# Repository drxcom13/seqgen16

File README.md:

# SeqGen16 – 16-kanałowy cyfrowy generator sekwencji (MAX 10 10M08 Eval Kit)

## Założenia projektu

1. **16 niezależnych kanałów** wyjściowych; każdy kanał to osobny blok w FPGA.
2. **Wyjścia cyfrowe 0/1** – na tym etapie bez wyjść analogowych. Na własnej płytce poziom wyjść (VCCB buforów TXU)
   ustawiany z PC: 1,8 / 2,5 / 3,3 / 4,0 / 5 V albo wyłączone (Hi-Z, stan po włączeniu zasilania).
3. **Sekwencja co najmniej 1024 zmian** na kanał; po końcu: powtórzenie N razy lub pętla.
4. **Rozdzielczość czasu (krok) od 1 ms do 1 s** – ostatecznie rozszerzona do **1 µs … 1 s**, ustawiana
   osobno dla każdego kanału.
5. **Wspólny start** – wybrane kanały ruszają w tym samym takcie zegara.
6. **Wyjścia synchronizujące:** zegar bazowy **BASE_CLK** zsynchronizowany z wyjściami oraz **SYNC**
   ze zboczem narastającym w chwili wyzwolenia sekwencji.
7. **Platforma:** płytka MAX 10 10M08 Evaluation Kit (10M08SAE144C8G).
8. **Architektura:** aplikacja PC (programator sekwencji) ↔ RS-232 ↔ procesor **Nios** w FPGA ↔ bloki
   generatorów (1 blok = 1 kanał).
9. **Źródła FPGA w VHDL.**
10. **Aplikacja PC po angielsku**, z możliwością **narysowania przebiegu każdego wyjścia** oraz
    importu i eksportu sekwencji do pliku.

## Architektura

*Schemat blokowy: [SVG](docs/schemat_blokowy.svg) · [PNG](docs/schemat_blokowy.png)*

- **PC** – aplikacja (GUI / CLI) buduje sekwencje i wysyła je ramkami z CRC16 przez konwerter USB-UART.
- **Nios V/c** w FPGA odbiera ramki przez UART, zapisuje konfigurację i kroki do generatora przez magistralę Avalon-MM.
- **seq_gen16** – 16 identycznych bloków `seq_channel` (każdy z własną pamięcią M9K 1024 kroki × 1 bit,
  sekwencerem i rejestrem wyjściowym), wspólna podstawa czasu 1 µs oraz generator BASE_CLK / SYNC.
- **Wyjścia** – cyfrowe 0/1: CH0–CH15, BASE_CLK, SYNC (piny w sekcji *Podłączenie*). FPGA pracuje w 3,3 V LVCMOS;
  na własnej płytce bufory TXU0104/TXU0102 przenoszą to na poziom VCCB (komenda SET_VOUT, wszystkie wyjścia razem).
- **USB-Blaster** (JTAG) służy tylko do wgrania obrazu FPGA (.sof / .pof).

## Spełnienie wymagań

| Wymaganie | Realizacja |
|---|---|
| 16 kanałów, każdy = 1 blok w FPGA | 16 × `seq_channel.vhd` w `seq_gen16.vhd` |
| rozdzielczość kroku 1 ms … 1 s | krok = N µs, od **1 µs** do 1 s (sprzęt do 1,048 s), wspólna podstawa 1 µs, ustawiany niezależnie dla każdego kanału |
| długość ≥ 1024 zmian | 1 … 1024 kroków na kanał, + powtarzanie 1…65535 razy lub w pętli |
| programowanie z PC | GUI (Tkinter, po angielsku) z edytorem do rysowania przebiegu każdego wyjścia myszą, CLI, projekt w JSON |
| Nios + RS-232 | Nios V/c, UART 115200 8N1, protokół binarny z CRC16 (`PROTOCOL.md`) |
| synchronizacja | kanały z jednej maski START ruszają w tym samym takcie 20 ns |

**Wyjścia:** wszystkie kanały są cyfrowe – w każdym kroku wyjście ma stan 0 lub 1. Po zatrzymaniu
kanał przyjmuje zadany poziom spoczynkowy (idle 0/1); po ostatnim powtórzeniu może trzymać ostatni
krok albo wrócić do poziomu idle.

**Wyjścia synchronizujące:**
- **BASE_CLK** – zegar bazowy o wypełnieniu 50 %, okres ustawiany z PC (2 µs … 2,1 s, domyślnie 1 ms).
  Nadaje tylko wtedy, gdy pracuje dowolny kanał (w spoczynku = 0). Każdy START go restartuje i zaczyna od zbocza
  narastającego, więc jego zbocza wypadają na granicach kroków. Przy ponownym starcie w trakcie pracy BASE_CLK
  i SYNC schodzą na 1 takt (20 ns) do 0, żeby zbocze narastające zawsze wypadło w chwili wyzwolenia.
- **SYNC** – zbocze narastające dokładnie w chwili wyzwolenia sekwencji; impuls o zadanej szerokości
  (domyślnie 1 ms) albo – przy szerokości 0 – stan wysoki, dopóki pracuje dowolny kanał.

Kanały, BASE_CLK i SYNC mają identyczne opóźnienie potokowe, a ich ostatnie rejestry są w komórkach I/O
(FAST_OUTPUT_REGISTER), więc zbocza są generowane w tym samym takcie zegara 50 MHz.
Rozrzut na złączach za buforami TXU wymaga pomiaru na prototypie. Aby go zmierzyć,
ustaw pierwszy krok wszystkich badanych kanałów na 1 po stanie spoczynkowym 0 i uruchom je jedną maską START.
Zmierz względem SYNC czas przejścia każdego wyjścia przez 50% jego amplitudy, także dla BASE_CLK.
Zapisz różnicę między najwcześniejszym i najpóźniejszym zboczem, napięcie VCCB i obciążenie wyjść.

**Start synchroniczny:** *Start enabled (synchronous)* wysyła jedną komendę START z maską wszystkich włączonych
kanałów, czyli jeden zapis do rejestru – wszystkie kanały z maski ruszają w tym samym takcie zegara. START restartuje
też podstawę czasu 1 µs, więc pierwszy krok trwa dokładnie zadany czas. Kanały uruchamiane osobno (*Start this
channel*) nie są ze sobą zsynchronizowane; START przesuwa też jednorazowo (< 1 µs) podstawę czasu kanałów już pracujących.

## Wyniki kompilacji (Quartus Prime Lite 25.1, sprawdzone)

| Zasób | Użycie |
|---|---|
| Logic elements | 5 604 / 8 064 (69 %) |
| Pamięć | 142 848 / 387 072 bit, **M9K 42 / 42 (100 %)** – pamięci 16 kanałów, 12 KB RAM Nios, kolejki testera |
| Timing @ 50 MHz | setup slack +7,747 ns, hold +0,286 ns (Slow 1200 mV, 85 °C) |

Wyniki dla pinów własnej płytki (10M08SAE144C8G, kolejność CH0–15 = piny 60…38, z testerem protokołów, 2026-11-25) według raportów
Fitter i Timing Analyzer (`quartus/output_files/seqgen16.fit.summary`, `seqgen16.sta.summary` – powstają przy
kompilacji, nie ma ich w repozytorium).
Wszystkie 18 wyjść (CH0-15, BASE_CLK, SYNC) ma
ostatni rejestr w komórce I/O (`FAST_OUTPUT_REGISTER`).

Wariant z Nios V/m (debuger JTAG, `build_fpga.ps1 -Cpu niosv_m`) też jest dostępny – zajmuje ok. 1,5–2 tys. LE więcej.

> **Nios II vs Nios V:** Quartus 25.1 nie zawiera już rdzenia Nios II Gen2 w Platform Designerze,
> dlatego użyty jest jego następca Nios V (RISC-V). Architektura systemu jest taka sama.

## Struktura

```
quartus/
  ip/seq_gen16/seq_channel.vhd   blok kanału
  ip/seq_gen16/seq_gen16.vhd     16 kanałów + slave Avalon-MM (mapa rejestrów w nagłówku)
  ip/seq_gen16/seq_gen16_hw.tcl  komponent Platform Designer
  seqgen16_top.vhd               top level (POR, LED-y)
  create_system.tcl              tworzy nios_sys.qsys (Nios V + RAM + UART + generator)
  seqgen16.qsf / .sdc            projekt, piny, timing
  build_fpga.ps1                 pełna budowa
fw/            firmware Nios V (bare-metal C, ~3 KB): main.c, hw.h, crt0.S, link.ld, build.ps1
pc/            seqgen.py (biblioteka), seqgen_gui.py, seqgen_cli.py, patterns.py, emulator.py,
               fw_sim.py (symulator RV32I firmware), test_seqgen.py, test_firmware.py
sim/           tb_seq_gen16.vhd + run_sim.do / run_sim.ps1 (Questa) – testbench samosprawdzający
examples/      demo_16ch.json
pcb/seqgen16/  projekt KiCad własnej płytki (w toku): arkusze FPGA, USB, Power, Outputs
docs/          schemat blokowy (SVG/PNG), zrzuty ekranu aplikacji
CLAUDE.md      notatki dla asystenta AI (Claude Code) – stan projektu, decyzje, pułapki
```

## Budowanie

> Quartus nie obsługuje ścieżek > 260 znaków – skopiuj projekt do krótkiej ścieżki, np. `C:\proj\seqgen16`.

1. **Toolchain firmware** – zainstaluj darmowy *Ashling RiscFree IDE for Altera FPGAs*
   (zawiera `riscv32-unknown-elf-gcc`). Jeśli nie jest w `C:\altera_lite\25.1std\riscfree`,
   ustaw `RISCV_TOOLCHAIN` na katalog `bin`.
2. Firmware → `quartus\onchip_ram.hex`:
   ```powershell
   .\fw\build.ps1
   ```
3. FPGA (Platform Designer + kompilacja, ~3 min):
   ```powershell
   .\quartus\build_fpga.ps1
   ```
4. Programowanie: `output_files\seqgen16.sof` (SRAM, do testów) lub `seqgen16.pof` (flash, zostaje po
   wyłączeniu zasilania) przez USB-Blaster na złączu JTAG J10.
   Późniejsze zmiany samego firmware bez ponownej kompilacji FPGA: `.\fw\build.ps1 -UpdateSof`.

## Podłączenie

Własna płytka jest projektowana dla JLCPCB, 4 warstwy, FR-4 Tg135, 1,6 mm, miedź 1 oz.
Przelotki przelotowe mają otwór 0,30 mm. Domyślna średnica pada wynosi 0,45 mm,
a w miejscach o ograniczonej przestrzeni można wybrać 0,40 mm.
Footprint J1 w bibliotece projektu ma cztery zewnętrzne pola GND skrócone od strony
kołków pozycjonujących o 0,08 mm. Otwory i rozstaw styków odpowiadają footprintowi GCT USB4105.

Przypisanie pinów dla **własnej płytki** (`pcb/seqgen16`). Nazwy w kolumnie „Sieć” to etykiety globalne na
schemacie (`fpga.kicad_sch`); przy zmianie pinów aktualizuj schemat i `quartus/seqgen16.qsf` razem.

| Sygnał | Pin FPGA | Sieć (KiCad) |
|---|---|---|
| clk_50 | 27 (CLK0p) | oscylator 50 MHz |
| reset_n (przycisk RESET, aktywny 0) | 121 (DEV_CLRn jako zwykłe wejście) | RESET_N |
| uart_txd (→ RX mostka USB) | 111 | TXD |
| uart_rxd (← TX mostka USB) | 110 | RXD |
| ch_out[0..7] | 60, 59, 58, 57, 56, 55, 54, 50 | CH0…CH7 |
| ch_out[8..15] | 47, 46, 45, 44, 43, 41, 39, 38 | CH8…CH15 |
| sync_out (SYNC) | 28 (CLK1n) | SYNC |
| clk_base (BASE_CLK) | 29 (CLK1p) | BASE_CLK |
| led_n[0] | 132 | LED1_N – LED1: heartbeat (~1,5 Hz) |
| led_n[1] | 134 | LED2_N – LED2: pracuje dowolny kanał |
| led_n[2..4] | 135, 140, 141 | na płytce niepodłączone – w FPGA na stałe wyłączone (stan 1) |

Kanały są w banku 3, UART w banku 4, SYNC/BASE_CLK w banku 2 (wszystkie VCCIO = 3,3 V).

**Reset:** wciśnięcie przycisku RESET (stan niski na `reset_n`) resetuje cały system – Nios (firmware startuje
od początku), UART i generator (kanały zatrzymane, wyjścia 0, konfiguracja domyślna, BASE_CLK/SYNC = 0).
Wejście jest synchronizowane, a reset trwa jeszcze 2,6 ms po zwolnieniu przycisku (odbicia styku są
filtrowane). Pin ma włączony wewnętrzny pull-up, więc niepodłączony nie blokuje pracy (np. na płytce
ewaluacyjnej). Logika: `quartus/reset_ctrl.vhd`, test: `sim/tb_reset_ctrl.vhd`.

### Tester protokołów – złącze J6 (SPI / I2C / UART TTL)

Złącze J6 (listwa 2×6, 2,54 mm, górna krawędź płytki) służy do testowania układów i portów szeregowych.
Na tym etapie SeqGen16 pracuje jako **SPI master** (tryby 0–3, do 12,5 MHz), **I2C master** (100 kHz / 400 kHz /
1 MHz; SCL: 3/5 okresu w stanie niskim, czasy zgodne z normą I2C, START, powtórzony START, ACK/NACK, rozciąganie zegara przez slave) i **UART** (8 bitów, parzystość N/E/O,
1 lub 2 bity stopu, do 3 Mbd). Tryby slave i podsłuch magistrali są zaplanowane jako kolejne etapy.

| Pin J6 | Sygnał | Pin J6 | Sygnał |
|---|---|---|---|
| 1 | PVCC (wyjście napięcia logiki) | 2 | GND |
| 3 | SCK | 4 | GND |
| 5 | MOSI | 6 | MISO |
| 7 | CS | 8 | GND |
| 9 | SDA | 10 | SCL |
| 11 | TX (wyjście UART) | 12 | RX (wejście UART) |

- **Poziom logiki J6 (PVCC):** osobny stabilizator U13 (TLV75801P, taki sam dzielnik jak VCCB): wyłączone,
  1,8 / 2,5 / 3,3 / 4,0 / ~5 V, ustawiany z PC niezależnie od poziomu wyjść CH. Po włączeniu zasilania i podczas
  konfiguracji FPGA PVCC jest wyłączone, a translatory nie sterują linii J6. Pin 1 nie powinien być łączony
  z zasilaniem układu, który ma własne zasilanie (przy wyłączeniu LDO rozładowuje wyjście przez 95 Ω).
- **Translatory:** SN74LVC1T45 na SCK, MOSI, CS, MISO, TX, RX (kierunek ustawia FPGA zależnie od trybu);
  I2C: tranzystory 2N7002 ściągają SDA/SCL do zera, stan linii czyta SN74LVC2T45 – działa przy każdym PVCC.
  Zworka **JP3** dołącza rezystory podciągające 2,2 kΩ SDA/SCL do PVCC (zdjąć przy magistrali z własnymi pull-upami).
  Na każdej linii rezystor 33 Ω i dioda TVS. Linie wejściowe mają 100 kΩ do poziomu spoczynkowego.
- **Próbkowanie MISO** można opóźnić o 0–7 taktów po 20 ns (domyślnie 1), co kompensuje translatory i kabel przy
  wysokich częstotliwościach SCK.

| Sygnał FPGA | Pin | Sieć | Sygnał FPGA | Pin | Sieć |
|---|---|---|---|---|---|
| pt_sck | 80 | PT_SCK | pt_rx | 98 | PT_RX |
| pt_mosi | 81 | PT_MOSI | pt_sda_in / pt_scl_in | 88 / 89 | PT_SDA_IN / PT_SCL_IN |
| pt_cs | 84 | PT_CS | pt_sda_drv / pt_scl_drv | 90 / 91 | PT_SDA_DRV / PT_SCL_DRV |
| pt_miso | 85 | PT_MISO | pvcc_off | 92 | PVCC_OFF |
| pt_dir_spi / pt_dir_miso | 86 / 87 | PT_DIR_SPI / PT_DIR_MISO | psel_2v5_n / psel_3v3_n / psel_5v_n | 93 / 96 / 97 | PSEL_* |
| pt_tx / pt_dir_tx | 77 / 79 | PT_TX / PT_DIR_TX | | | |

Banki 5 i 6 (VCCIO = 3,3 V). Na płytce ewaluacyjnej te piny prowadzą do innych układów – przed wgraniem obrazu
z testerem na płytkę ewaluacyjną należy sprawdzić, co jest do nich podłączone.

Obsługa: okno **Serial tester (J6)…** w GUI (wysyłanie w HEX lub jako tekst, log odebranych danych, skan I2C,
ciągły odbiór UART) albo CLI:

```powershell
python pc\seqgen_cli.py -p COM5 spi "9F 00 00 00" --hz 1e6 --mode 0 --level 3.3   # odczyt JEDEC ID pamięci SPI
python pc\seqgen_cli.py -p COM5 i2c-scan --level 3.3
python pc\seqgen_cli.py -p COM5 i2c 0x50 --write "00 10" --read 4                 # zapis wskaźnika, odczyt 4 bajtów
python pc\seqgen_cli.py -p COM5 uart '"AT\r\n"' --baud 115200 --wait 200           # wysłanie i odbiór odpowiedzi
python pc\seqgen_cli.py -p COM5 pins                                               # stan linii J6
```

W bibliotece: `SeqGen.spi_transfer()`, `i2c_transfer()`, `i2c_scan()`, `uart_send()`, `uart_receive()`
(protokół: komendy 0x40–0x45 w `PROTOCOL.md`). Emulator (`EMU`) symuluje mostek MOSI→MISO i TX→RX oraz pamięć
EEPROM I2C pod adresem 0x50.

**Płytka MAX 10 10M08 Evaluation Kit:** poprzednie przypisanie (UART na Arduino D0/D1, CH0–11 na Arduino D2–D13,
CH12–15 / BASE_CLK / SYNC na J8) jest w historii git – `git show 22c6dcf:quartus/seqgen16.qsf` i
`git show 22c6dcf:README.md`.

## Obsługa aplikacji PC (interfejs po angielsku)

```powershell
pip install pyserial
python pc\seqgen_gui.py                                    # GUI; port "EMU" = emulator bez sprzętu
```

Okno składa się z czterech części:

| Obszar | Co zawiera |
|---|---|
| **Pasek górny** | wybór portu (`COMx` lub `EMU`), *Connect / Disconnect*, informacja o urządzeniu; *New / Open / Save / Save As* projektu |
| **Tabela kanałów (lewo)** | nazwa, włączenie (kliknij **On**), krok, liczba kroków, powtórzenia i stan na żywo (`RUN n` = aktualny krok, `DONE`, `stop`); *Enable all / Disable all*; panel **Sync outputs (J8)** z okresem BASE_CLK i szerokością SYNC; panel **Output level** (off / 1,8 … 5 V – wysyłany przy uploadzie i od razu po zmianie, gdy połączono) |
| **Edytor kanału (środek)** | ustawienia wybranego kanału i jego przebieg do rysowania myszą, narzędzia edycji i generatory |
| **Podgląd (dół)** | wszystkie 16 kanałów oraz BASE_CLK i SYNC na wspólnej osi czasu (t = 0 to chwila startu); zielone diody = bieżący stan wyjść; kliknięcie ścieżki wybiera kanał |

### Typowa praca

1. Wybierz port konwertera USB-UART (lub `EMU`, żeby pracować bez płytki) i kliknij **Connect**.
2. Wybierz kanał w tabeli, ustaw **Step** (z jednostką µs / ms / s), **Length**, **Repeat** i poziom **Idle**.
3. Narysuj przebieg w edytorze albo wygeneruj go (*Clock*, *Pulse*, *Random*) lub wczytaj (*Import file…*).
4. Włącz potrzebne kanały (kolumna **On**) i ustaw BASE_CLK / SYNC.
5. **Upload all enabled** – wysyła ustawienia i sekwencje oraz sprawdza je odczytem z urządzenia.
6. **▶ Start enabled (synchronous)** – wszystkie włączone kanały ruszają w tym samym takcie; **■ Stop all** zatrzymuje.
7. **Save** zapisuje cały projekt (JSON), **Export file…** – sekwencję jednego kanału (.txt / .csv).

### Edytor przebiegu

Niebieski obszar to zaznaczenie (tu kroki 20…35), czerwona linia – krok, który urządzenie właśnie odtwarza.
Nad wykresem: numery kroków i czas od początku sekwencji; przerywana linia na końcu – koniec sekwencji
i co dzieje się dalej (`loop`, `x3, then hold` itp.).

| Akcja | Jak |
|---|---|
| rysowanie stanu 1 / 0 | przeciągnij lewym / prawym przyciskiem myszy po krokach |
| zaznaczenie zakresu | Shift + przeciągnięcie (Esc – odznacz, Ctrl+A – wszystko) |
| przewijanie / powiększenie | kółko myszy / Ctrl + kółko, przyciski Zoom +/−, Fit |
| cofnij | Ctrl+Z lub *Undo* (200 kroków wstecz) |
| operacje na zaznaczeniu (lub całości) | *Set 1*, *Set 0*, *Invert*, *◀ Shift / Shift ▶* (rotacja), *Copy / Paste* |
| generatory | *Clock* (High/Low/Phase w krokach), *Pulse* (Start/Width), *Random* (gęstość) |
| import / eksport | *Import file…* / *Export file…*: tekst `0101…` (.txt) lub CSV `level,time_ms` (.csv) – eksport wczytuje się z powrotem bez zmian; przy imporcie CSV liczy się pierwsza kolumna (≠ 0 → 1), linie `#` to komentarze; *Paste text*, *Copy as text* |
| kopiowanie na inne kanały | *Copy to channels…* (opcjonalnie z ustawieniami czasu) |

Parametry kanału: nazwa, włączony, czas kroku (1 µs … 1 s, rozdzielczość 1 µs; pole z wyborem jednostki
µs / ms / s – tak samo dla BASE_CLK i SYNC), długość (1…1024 kroki), liczba powtórzeń (0 = w pętli),
poziom idle, zachowanie po ostatnim powtórzeniu (*hold last step* / *go to idle level*).

Projekt JSON (wersja 3): `clock_period_ms`, `sync_width_ms` oraz dla każdego kanału `name`, `enabled`, `period_ms`, `loops`, `idle`, `idle_on_done`,
`steps` (lista 0/1). Upload weryfikuje zawartość pamięci odczytem; pełne 16 × 1024 kroków ≈ 2 s przy 115200 bd.

### Linia poleceń (CLI)

```powershell
python pc\seqgen_cli.py ports
python pc\seqgen_cli.py -p COM5 upload examples\demo_16ch.json --start
python pc\seqgen_cli.py -p COM5 status
python pc\seqgen_cli.py -p COM5 stop all
python pc\seqgen_cli.py -p COM5 vout 3.3                  # poziom wyjść: off, 1.8, 2.5, 3.3, 4.0, 5.0 (bez wartości = odczyt)
python pc\seqgen_cli.py show examples\demo_16ch.json       # podgląd sekwencji jako 0/1
```

Tester protokołów (J6): komendy `pt-level`, `spi`, `i2c`, `i2c-scan`, `uart`, `pins` – przykłady w sekcji
*Tester protokołów* wyżej i w `python pc\seqgen_cli.py -h`.

Testy: `cd pc ; python -m unittest test_seqgen test_firmware -v` (`test_firmware` uruchamia zbudowany `fw/build/fw.bin`).

## Stan weryfikacji

- ✅ Pełna kompilacja Quartus (synteza, fitter, timing, .sof/.pof) dla VHDL + Nios V/c.
- ✅ Firmware 2.3: zbudowany toolchainem RiscFree (GCC 13.2, RV32I) – 4,0 KB kodu + 2,3 KB danych w 12 KB RAM, wpisany do `seqgen16.sof/.pof`.
- ✅ Firmware wykonany w symulatorze zestawu instrukcji RV32I (`pc/fw_sim.py`) z modelami UART i rejestrów generatora: 18 testów (`pc/test_firmware.py`) przez prawdziwą bibliotekę PC – protokół, konfiguracja rejestrów, zapis/odczyt 1024 kroków, pętle, błędne CRC, śmieci na linii, nieznane komendy. Obsługa jednego odebranego bajtu to ~115 instrukcji, czyli kilkukrotny zapas względem 86,8 µs na bajt przy 115200 bd.
- ✅ Aplikacja PC: 40 testów (biblioteka na emulatorze + te same scenariusze na firmware, m.in. krok 1 µs, eksport/import)
  + automatyczny test GUI (rysowanie, zaznaczanie, generator, undo, włączanie kanałów w tabeli, pola czasu µs/ms/s,
  BASE_CLK/SYNC, eksport/import pliku, upload, start) i CLI na emulatorze.
- ✅ Symulacja RTL w Questa: `sim/run_sim.ps1` → **TEST PASSED** (zapis/odczyt 1024 kroków, stany i czasy kroków,
  pętle i zakończenie, synchronizacja kanałów co do taktu, STOP, poziom idle, krok 1 ms = dokładnie 50 000 taktów, krok 1 µs = 1000 ns,
  zbocza SYNC / BASE_CLK w tym samym czasie co zmiany kanałów – także przy ponownym starcie). Symulacja wykryła
  i pomogła usunąć błąd: BASE_CLK będący w stanie 1 w chwili START nie dawał zbocza narastającego.
- ⚠️ Nie testowano na sprzęcie.

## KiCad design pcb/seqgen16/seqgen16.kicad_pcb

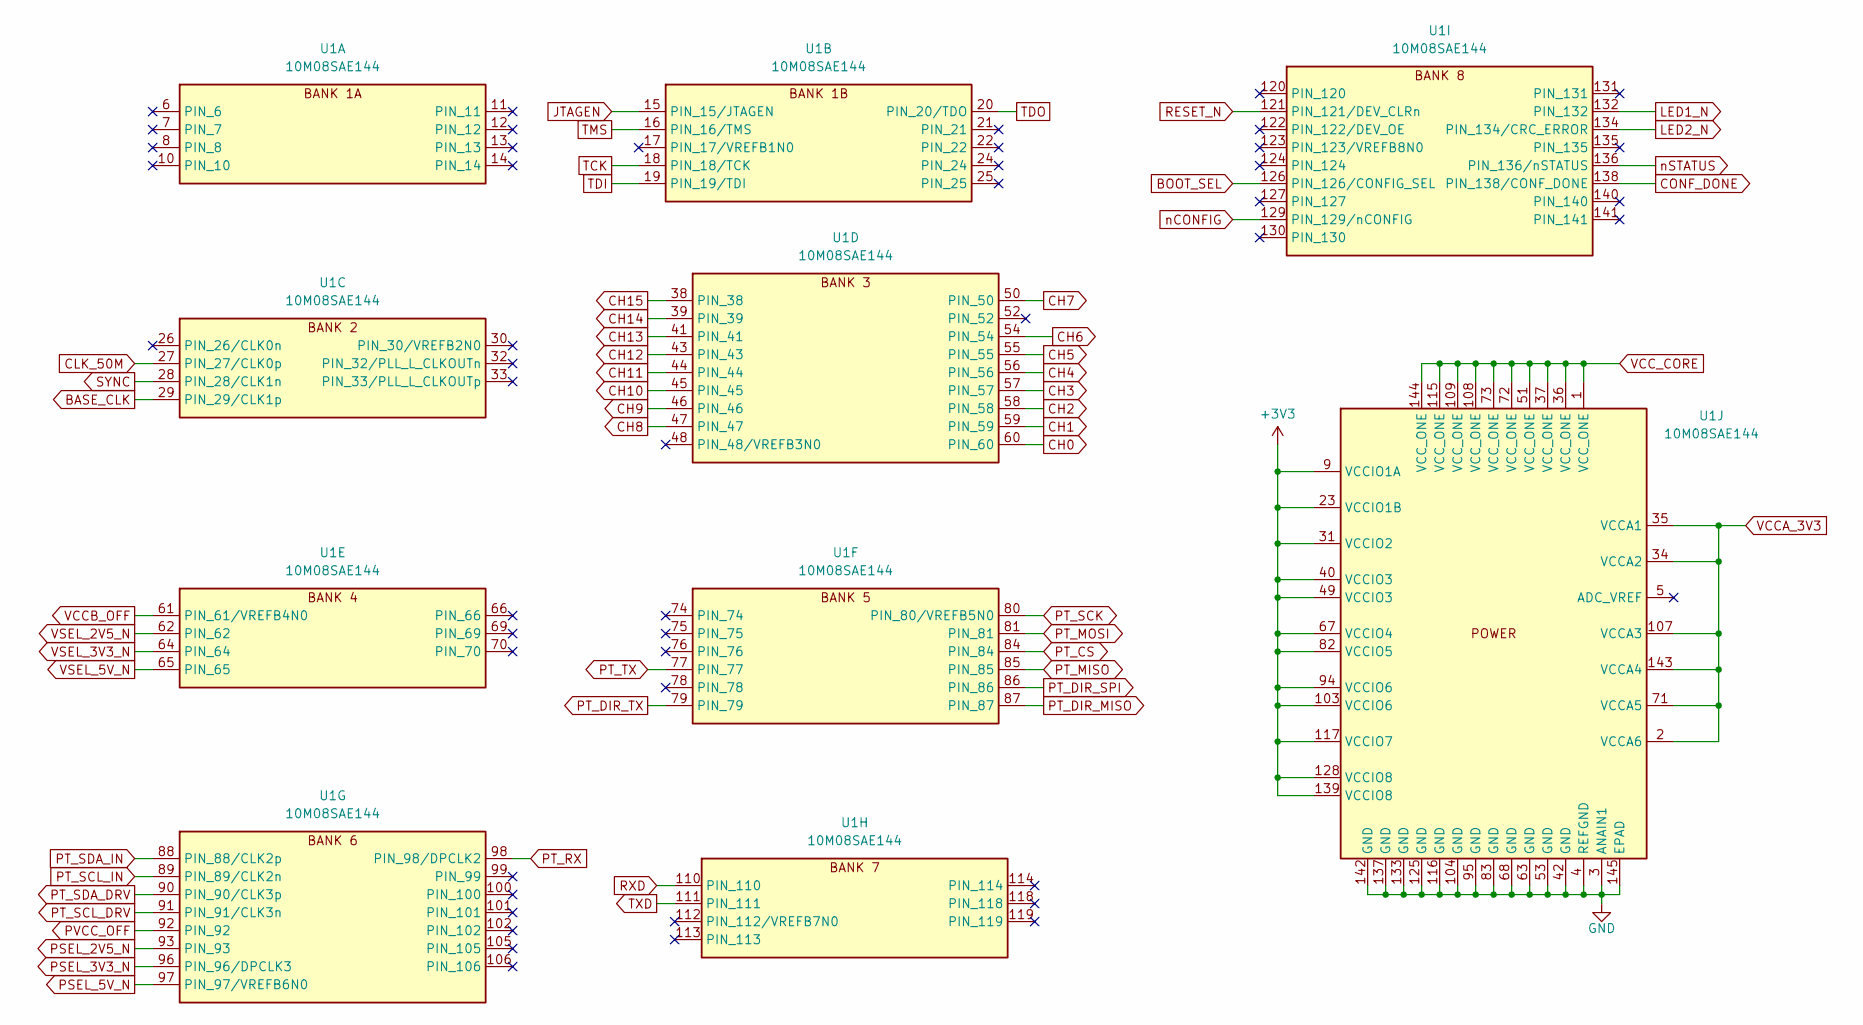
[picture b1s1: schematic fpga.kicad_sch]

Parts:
U1: 10M08SAE144; EQFP-144-1EP_20x20mm_P0.5mm_EP5x5mm

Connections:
+3V3: U1.9 (VCCIO1A), U1.23 (VCCIO1B), U1.31 (VCCIO2), U1.40 (VCCIO3), U1.49 (VCCIO3), U1.67 (VCCIO4), U1.82 (VCCIO5), U1.94 (VCCIO6), U1.103 (VCCIO6), U1.117 (VCCIO7), U1.128 (VCCIO8), U1.139 (VCCIO8); also elsewhere on the board
BASE_CLK: U1.29 (PIN_29/CLK1p); also elsewhere on the board
BOOT_SEL: U1.126 (PIN_126/CONFIG_SEL); also elsewhere on the board
CH0: U1.60 (PIN_60); also elsewhere on the board
CH1: U1.59 (PIN_59); also elsewhere on the board
CH2: U1.58 (PIN_58); also elsewhere on the board
CH3: U1.57 (PIN_57); also elsewhere on the board
CH4: U1.56 (PIN_56); also elsewhere on the board
CH5: U1.55 (PIN_55); also elsewhere on the board
CH6: U1.54 (PIN_54); also elsewhere on the board
CH7: U1.50 (PIN_50); also elsewhere on the board
CH8: U1.47 (PIN_47); also elsewhere on the board
CH9: U1.46 (PIN_46); also elsewhere on the board
CH10: U1.45 (PIN_45); also elsewhere on the board
CH11: U1.44 (PIN_44); also elsewhere on the board
CH12: U1.43 (PIN_43); also elsewhere on the board
CH13: U1.41 (PIN_41); also elsewhere on the board
CH14: U1.39 (PIN_39); also elsewhere on the board
CH15: U1.38 (PIN_38); also elsewhere on the board
CLK_50M: U1.27 (PIN_27/CLK0p); also elsewhere on the board
CONF_DONE: U1.138 (PIN_138/CONF_DONE); also elsewhere on the board
GND: U1.3 (ANAIN1), U1.4 (REFGND), U1.42 (GND), U1.53 (GND), U1.63 (GND), U1.68 (GND), U1.83 (GND), U1.95 (GND), U1.104 (GND), U1.116 (GND), U1.125 (GND), U1.133 (GND), U1.137 (GND), U1.142 (GND), U1.145 (EPAD); also elsewhere on the board
JTAGEN: U1.15 (PIN_15/JTAGEN); also elsewhere on the board
LED1_N: U1.132 (PIN_132); also elsewhere on the board
LED2_N: U1.134 (PIN_134/CRC_ERROR); also elsewhere on the board
PSEL_2V5_N: U1.93 (PIN_93); also elsewhere on the board
PSEL_3V3_N: U1.96 (PIN_96/DPCLK3); also elsewhere on the board
PSEL_5V_N: U1.97 (PIN_97/VREFB6N0); also elsewhere on the board
PT_CS: U1.84 (PIN_84); also elsewhere on the board
PT_DIR_MISO: U1.87 (PIN_87); also elsewhere on the board
PT_DIR_SPI: U1.86 (PIN_86); also elsewhere on the board
PT_DIR_TX: U1.79 (PIN_79); also elsewhere on the board
PT_MISO: U1.85 (PIN_85); also elsewhere on the board
PT_MOSI: U1.81 (PIN_81); also elsewhere on the board
PT_RX: U1.98 (PIN_98/DPCLK2); also elsewhere on the board
PT_SCK: U1.80 (PIN_80/VREFB5N0); also elsewhere on the board
PT_SCL_DRV: U1.91 (PIN_91/CLK3n); also elsewhere on the board
PT_SCL_IN: U1.89 (PIN_89/CLK2n); also elsewhere on the board
PT_SDA_DRV: U1.90 (PIN_90/CLK3p); also elsewhere on the board
PT_SDA_IN: U1.88 (PIN_88/CLK2p); also elsewhere on the board
PT_TX: U1.77 (PIN_77); also elsewhere on the board
PVCC_OFF: U1.92 (PIN_92); also elsewhere on the board
RESET_N: U1.121 (PIN_121/DEV_CLRn); also elsewhere on the board
RXD: U1.110 (PIN_110); also elsewhere on the board
SYNC: U1.28 (PIN_28/CLK1n); also elsewhere on the board
TCK: U1.18 (PIN_18/TCK); also elsewhere on the board
TDI: U1.19 (PIN_19/TDI); also elsewhere on the board
TDO: U1.20 (PIN_20/TDO); also elsewhere on the board
TMS: U1.16 (PIN_16/TMS); also elsewhere on the board
TXD: U1.111 (PIN_111); also elsewhere on the board
VCCA_3V3: U1.2 (VCCA6), U1.34 (VCCA2), U1.35 (VCCA1), U1.71 (VCCA5), U1.107 (VCCA3), U1.143 (VCCA4); also elsewhere on the board
VCCB_OFF: U1.61 (PIN_61/VREFB4N0); also elsewhere on the board
VCC_CORE: U1.1 (VCC_ONE), U1.36 (VCC_ONE), U1.37 (VCC_ONE), U1.51 (VCC_ONE), U1.72 (VCC_ONE), U1.73 (VCC_ONE), U1.108 (VCC_ONE), U1.109 (VCC_ONE), U1.115 (VCC_ONE), U1.144 (VCC_ONE); also elsewhere on the board
VSEL_2V5_N: U1.62 (PIN_62); also elsewhere on the board
VSEL_3V3_N: U1.64 (PIN_64); also elsewhere on the board
VSEL_5V_N: U1.65 (PIN_65); also elsewhere on the board
nCONFIG: U1.129 (PIN_129/nCONFIG); also elsewhere on the board
nSTATUS: U1.136 (PIN_136/nSTATUS); also elsewhere on the board

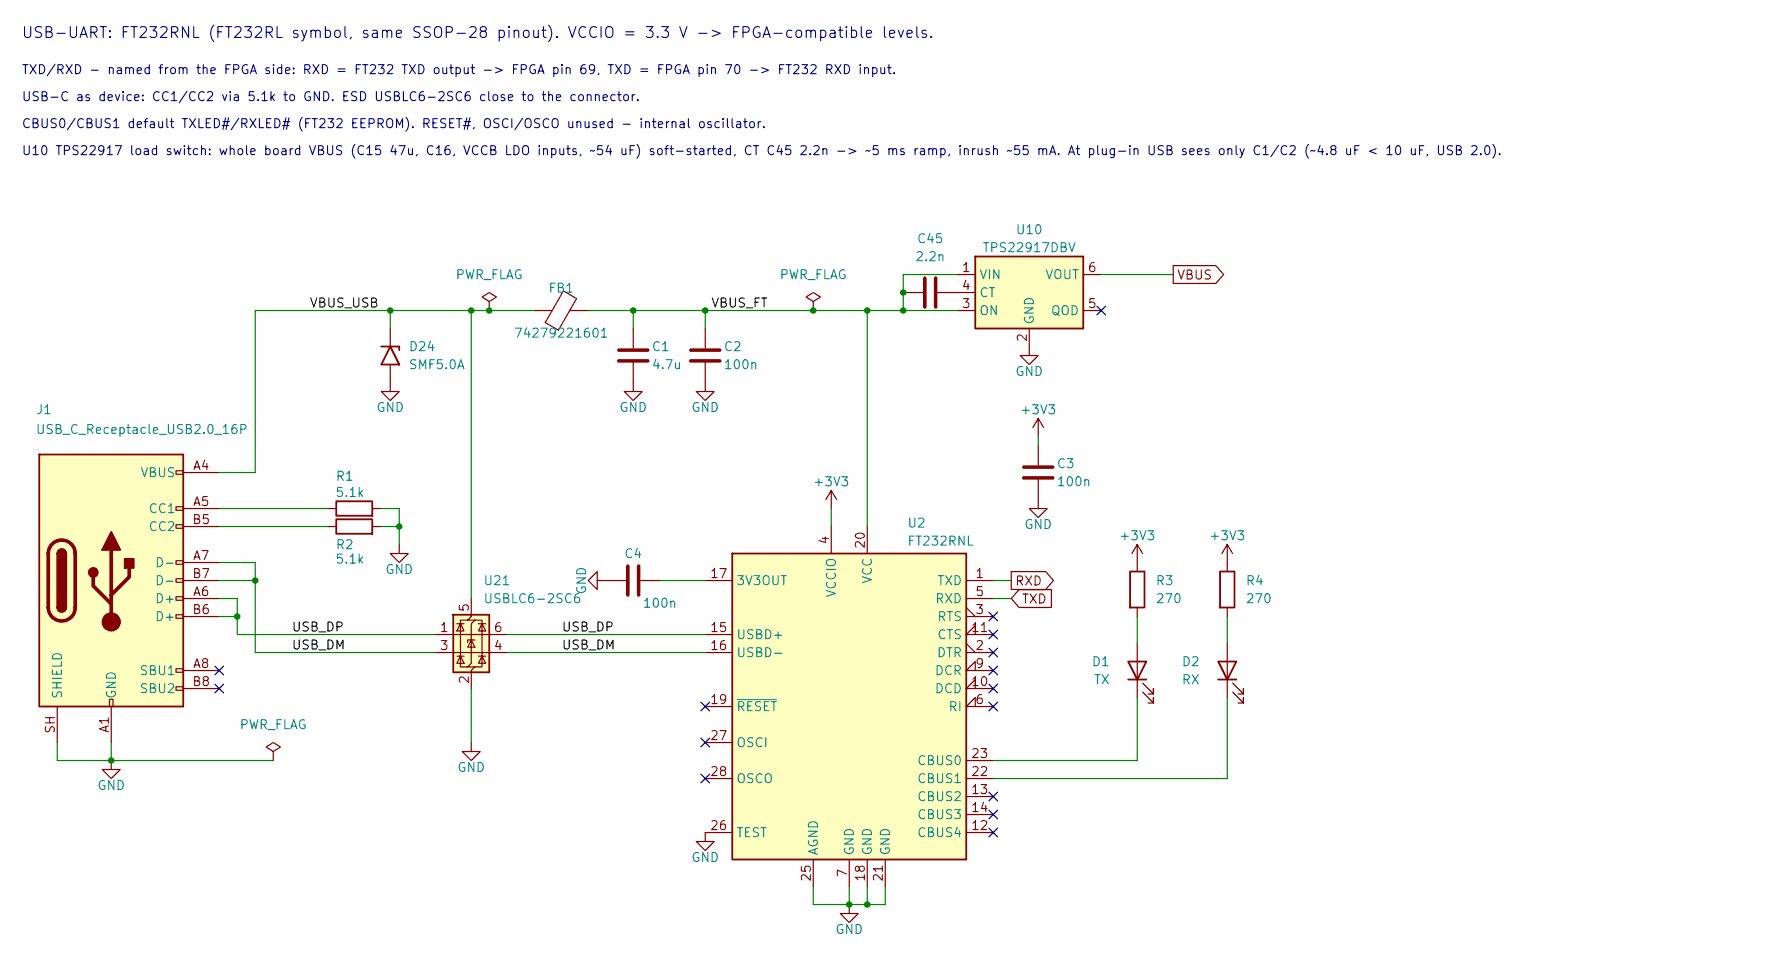
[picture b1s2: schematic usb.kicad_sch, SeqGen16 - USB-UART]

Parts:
C1: 4.7u; C_0805_2012Metric
C2, C3, C4: 100n; C_0603_1608Metric
C45: 2.2n; C_0603_1608Metric
D1: TX; LED_0603_1608Metric
D2: RX; LED_0603_1608Metric
D24: SMF5.0A; D_SMF
FB1: 74279221601; L_1206_3216Metric
J1: USB_C_Receptacle_USB2.0_16P; USB4105_16P_NPTH_Clearance
R1, R2: 5.1k; R_0603_1608Metric
R3, R4: 270; R_0603_1608Metric
U2: FT232RNL; SSOP-28_5.3x10.2mm_P0.65mm
U10: TPS22917DBV; SOT-23-6
U21: USBLC6-2SC6; SOT-23-6

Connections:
+3V3: C3.1, R3.1, R4.1, U2.4 (VCCIO); also elsewhere on the board
/USB/USB_DM: J1.A7 (D-), J1.B7 (D-), U2.16 (USBD-), U21.3 (I/O2), U21.4 (I/O2)
/USB/USB_DP: J1.A6 (D+), J1.B6 (D+), U2.15 (USBD+), U21.1 (I/O1), U21.6 (I/O1)
/USB/VBUS_FT: C1.1, C2.1, C45.1, FB1.2, U2.20 (VCC), U10.1 (VIN), U10.3 (ON)
/USB/VBUS_USB: D24.1 (A1), FB1.1, J1.A4 (VBUS), J1.A9 (VBUS), J1.B4 (VBUS), J1.B9 (VBUS), U21.5 (VBUS)
GND: C1.2, C2.2, C3.2, C4.2, D24.2 (A2), J1.A1 (GND), J1.A12 (GND), J1.B1 (GND), J1.B12 (GND), J1.SH (SHIELD), R1.2, R2.2, U2.7 (GND), U2.18 (GND), U2.21 (GND), U2.25 (AGND), U2.26 (TEST), U10.2 (GND), U21.2 (GND); also elsewhere on the board
unnamed: D1.2 (A), R3.2
unnamed: D1.1 (K), U2.23 (CBUS0)
unnamed: D2.2 (A), R4.2
unnamed: D2.1 (K), U2.22 (CBUS1)
unnamed: J1.A5 (CC1), R1.1
unnamed: J1.B5 (CC2), R2.1
unnamed: C4.1, U2.17 (3V3OUT)
unnamed: C45.2, U10.4 (CT)
RXD: U2.1 (TXD); also elsewhere on the board
TXD: U2.5 (RXD); also elsewhere on the board
VBUS: U10.6 (VOUT); also elsewhere on the board

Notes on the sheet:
U10 TPS22917 load switch: whole board VBUS (C15 47u, C16, VCCB LDO inputs, ~54 uF) soft-started, CT C45 2.2n -> ~5 ms ramp, inrush ~55 mA. At plug-in USB sees only C1/C2 (~4.8 uF < 10 uF, USB 2.0).
USB-C as device: CC1/CC2 via 5.1k to GND. ESD USBLC6-2SC6 close to the connector.
CBUS0/CBUS1 default TXLED#/RXLED# (FT232 EEPROM). RESET#, OSCI/OSCO unused - internal oscillator.
TXD/RXD - named from the FPGA side: RXD = FT232 TXD output -> FPGA pin 69, TXD = FPGA pin 70 -> FT232 RXD input.
USB-UART: FT232RNL (FT232RL symbol, same SSOP-28 pinout). VCCIO = 3.3 V -> FPGA-compatible levels.

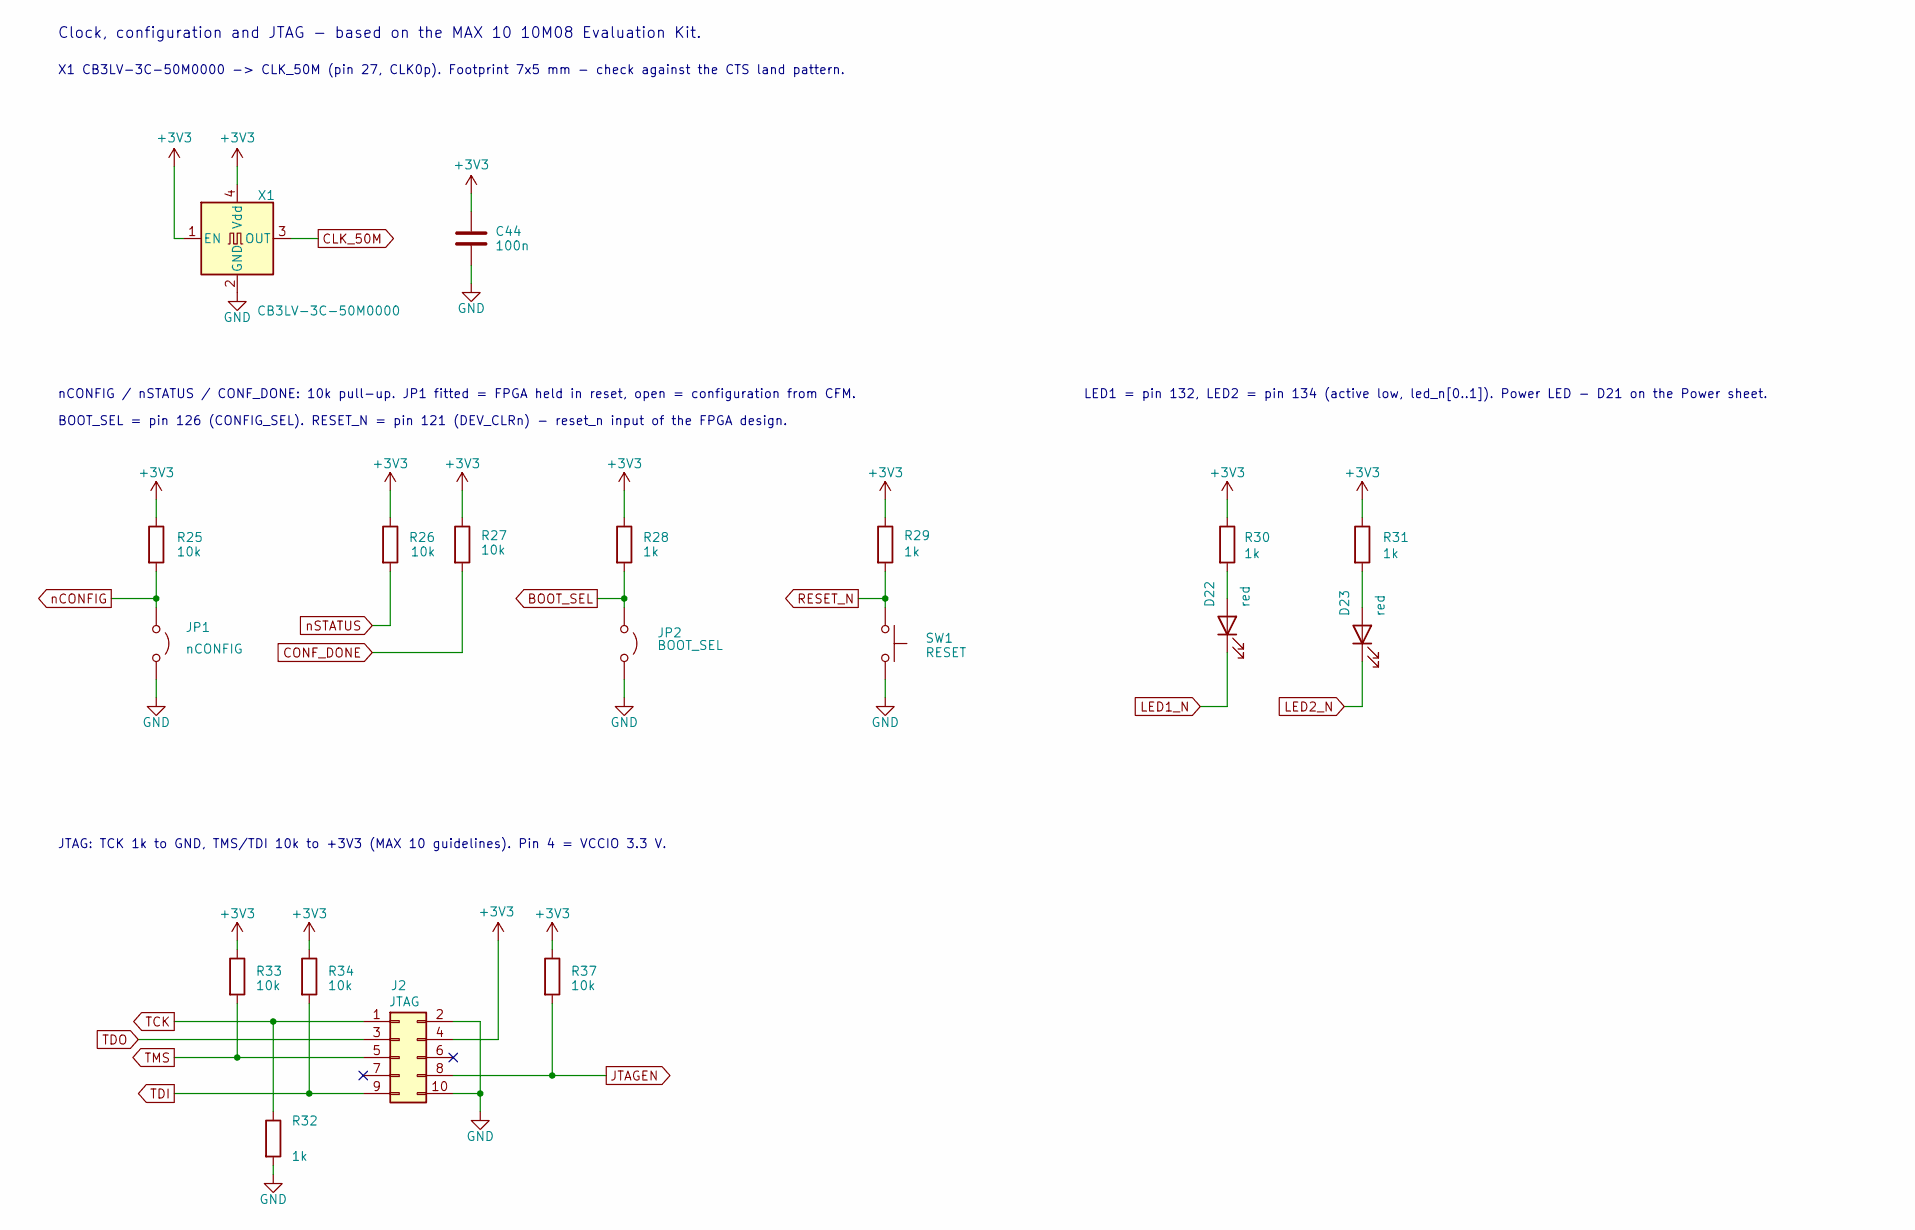
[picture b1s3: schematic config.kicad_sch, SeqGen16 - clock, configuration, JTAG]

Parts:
C44: 100n; C_0603_1608Metric
D22, D23: red; LED_0603_1608Metric
J2: JTAG; PinHeader_2x05_P2.54mm_Vertical
JP1: nCONFIG; PinHeader_1x02_P2.54mm_Vertical
JP2: BOOT_SEL; PinHeader_1x02_P2.54mm_Vertical
R25, R26, R27, R33, R34, R37: 10k; R_0603_1608Metric
R28, R29, R30, R31, R32: 1k; R_0603_1608Metric
SW1: RESET; SW_SPST_PTS645Sx43SMTR92
X1: CB3LV-3C-50M0000; Oscillator_SMD_SeikoEpson_SG8002CA-4Pin_7.0x5.0mm

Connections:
+3V3: C44.1, J2.4, R25.1, R26.1, R27.1, R28.1, R29.1, R30.1, R31.1, R33.1, R34.1, R37.1, X1.1 (EN), X1.4 (Vdd); also elsewhere on the board
BOOT_SEL: JP2.1 (A), R28.2; also elsewhere on the board
CLK_50M: X1.3 (OUT); also elsewhere on the board
CONF_DONE: R27.2; also elsewhere on the board
GND: C44.2, J2.2, J2.10, JP1.2 (B), JP2.2 (B), R32.2, SW1.2, X1.2 (GND); also elsewhere on the board
JTAGEN: J2.8, R37.2; also elsewhere on the board
LED1_N: D22.1 (K); also elsewhere on the board
LED2_N: D23.1 (K); also elsewhere on the board
unnamed: D22.2 (A), R30.2
unnamed: D23.2 (A), R31.2
RESET_N: R29.2, SW1.1; also elsewhere on the board
TCK: J2.1, R32.1; also elsewhere on the board
TDI: J2.9, R34.2; also elsewhere on the board
TDO: J2.3; also elsewhere on the board
TMS: J2.5, R33.2; also elsewhere on the board
nCONFIG: JP1.1 (A), R25.2; also elsewhere on the board
nSTATUS: R26.2; also elsewhere on the board

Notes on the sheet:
Clock, configuration and JTAG - based on the MAX 10 10M08 Evaluation Kit.
nCONFIG / nSTATUS / CONF_DONE: 10k pull-up. JP1 fitted = FPGA held in reset, open = configuration from CFM.
X1 CB3LV-3C-50M0000 -> CLK_50M (pin 27, CLK0p). Footprint 7x5 mm - check against the CTS land pattern.
LED1 = pin 132, LED2 = pin 134 (active low, led_n[0..1]). Power LED - D21 on the Power sheet.
JTAG: TCK 1k to GND, TMS/TDI 10k to +3V3 (MAX 10 guidelines). Pin 4 = VCCIO 3.3 V.
BOOT_SEL = pin 126 (CONFIG_SEL). RESET_N = pin 121 (DEV_CLRn) - reset_n input of the FPGA design.

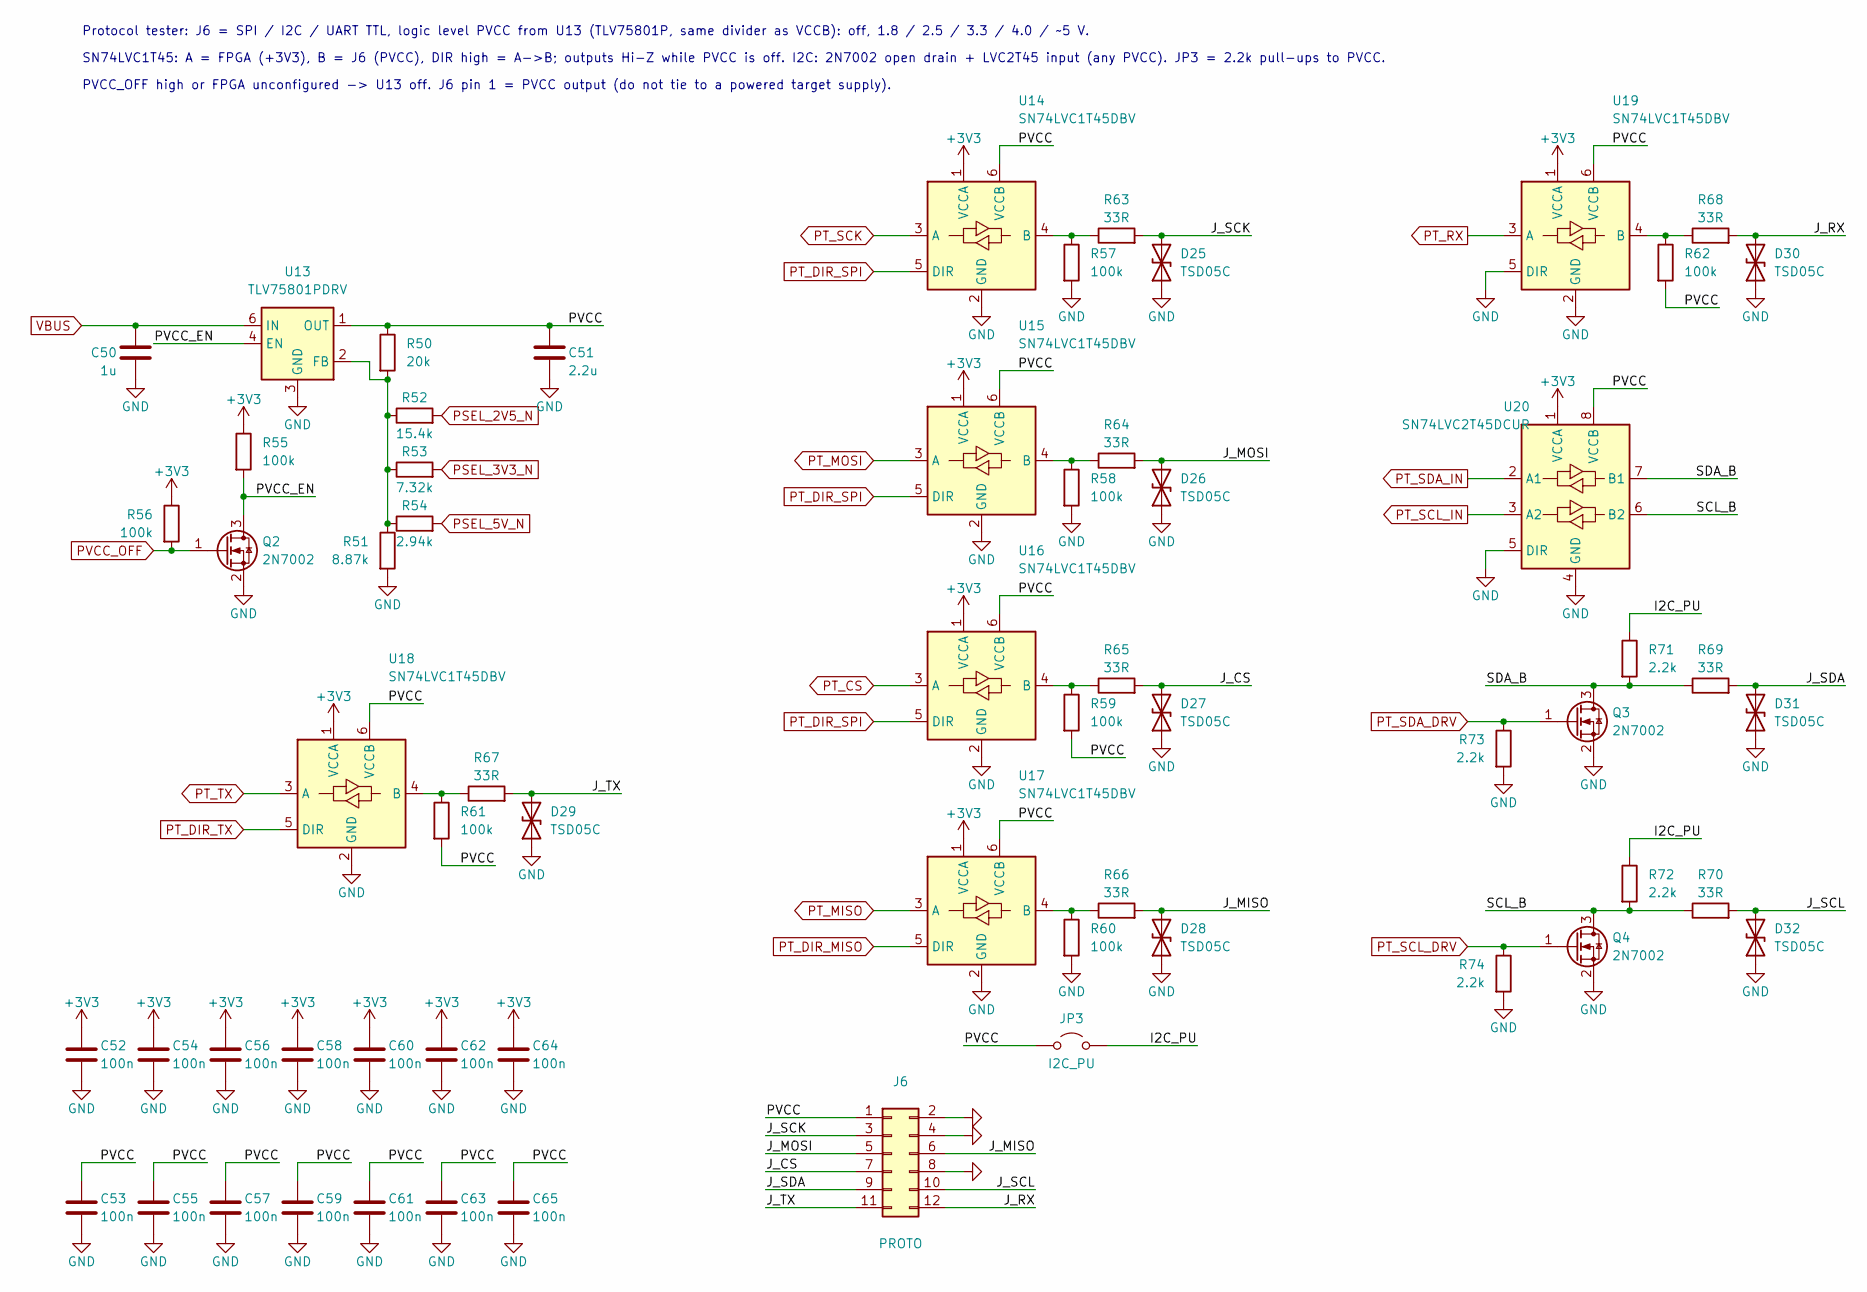
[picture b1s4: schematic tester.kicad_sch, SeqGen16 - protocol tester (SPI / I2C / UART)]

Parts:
C50: 1u; C_0603_1608Metric
C51: 2.2u; C_0603_1608Metric
C52, C53, C54, C55, C56, C57, C58, C59, C60, C61, C62, C63, C64, C65: 100n; C_0603_1608Metric
D25, D26, D27, D28, D29, D30, D31, D32: TSD05C; D_SOD-323
J6: PROTO; PinHeader_2x06_P2.54mm_Vertical
JP3: I2C_PU; PinHeader_1x02_P2.54mm_Vertical
Q2, Q3, Q4: 2N7002; SOT-23
R50: 20k; R_0603_1608Metric
R51: 8.87k; R_0603_1608Metric
R52: 15.4k; R_0603_1608Metric
R53: 7.32k; R_0603_1608Metric
R54: 2.94k; R_0603_1608Metric
R55, R56, R57, R58, R59, R60, R61, R62: 100k; R_0603_1608Metric
R63, R64, R65, R66, R67, R68, R69, R70: 33R; R_0603_1608Metric
R71, R72, R73, R74: 2.2k; R_0603_1608Metric
U13: TLV75801PDRV; WSON-6-1EP_2x2mm_P0.65mm_EP1x1.6mm
U14, U15, U16, U17, U18, U19: SN74LVC1T45DBV; SOT-23-6
U20: SN74LVC2T45DCUR; VSSOP-8_2.3x2mm_P0.5mm

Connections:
+3V3: C52.1, C54.1, C56.1, C58.1, C60.1, C62.1, C64.1, R55.1, R56.1, U14.1 (VCCA), U15.1 (VCCA), U16.1 (VCCA), U17.1 (VCCA), U18.1 (VCCA), U19.1 (VCCA), U20.1 (VCCA); also elsewhere on the board
/Protocol tester/I2C_PU: JP3.2 (B), R71.1, R72.1
/Protocol tester/J_CS: D27.2 (A2), J6.7, R65.2
/Protocol tester/J_MISO: D28.2 (A2), J6.6, R66.2
/Protocol tester/J_MOSI: D26.2 (A2), J6.5, R64.2
/Protocol tester/J_RX: D30.2 (A2), J6.12, R68.2
/Protocol tester/J_SCK: D25.2 (A2), J6.3, R63.2
/Protocol tester/J_SCL: D32.2 (A2), J6.10, R70.2
/Protocol tester/J_SDA: D31.2 (A2), J6.9, R69.2
/Protocol tester/J_TX: D29.2 (A2), J6.11, R67.2
/Protocol tester/PVCC: C51.1, C53.1, C55.1, C57.1, C59.1, C61.1, C63.1, C65.1, J6.1, JP3.1 (A), R50.1, R59.2, R61.2, R62.2, U13.1 (OUT), U14.6 (VCCB), U15.6 (VCCB), U16.6 (VCCB), U17.6 (VCCB), U18.6 (VCCB), U19.6 (VCCB), U20.8 (VCCB)
/Protocol tester/PVCC_EN: Q2.3 (D), R55.2, U13.4 (EN)
/Protocol tester/SCL_B: Q4.3 (D), R70.1, R72.2, U20.6 (B2)
/Protocol tester/SDA_B: Q3.3 (D), R69.1, R71.2, U20.7 (B1)
GND: C50.2, C51.2, C52.2, C53.2, C54.2, C55.2, C56.2, C57.2, C58.2, C59.2, C60.2, C61.2, C62.2, C63.2, C64.2, C65.2, D25.1 (A1), D26.1 (A1), D27.1 (A1), D28.1 (A1), D29.1 (A1), D30.1 (A1), D31.1 (A1), D32.1 (A1), J6.2, J6.4, J6.8, Q2.2 (S), Q3.2 (S), Q4.2 (S), R51.2, R57.2, R58.2, R60.2, R73.2, R74.2, U13.3 (GND), U13.7 (GND), U14.2 (GND), U15.2 (GND), U16.2 (GND), U17.2 (GND), U18.2 (GND), U19.2 (GND), U19.5 (DIR), U20.4 (GND), U20.5 (DIR); also elsewhere on the board
unnamed: R50.2, R51.1, R52.1, R53.1, R54.1, U13.2 (FB)
unnamed: R57.1, R63.1, U14.4 (B)
unnamed: R58.1, R64.1, U15.4 (B)
unnamed: R59.1, R65.1, U16.4 (B)
unnamed: R60.1, R66.1, U17.4 (B)
unnamed: R61.1, R67.1, U18.4 (B)
unnamed: R62.1, R68.1, U19.4 (B)
PSEL_2V5_N: R52.2; also elsewhere on the board
PSEL_3V3_N: R53.2; also elsewhere on the board
PSEL_5V_N: R54.2; also elsewhere on the board
PT_CS: U16.3 (A); also elsewhere on the board
PT_DIR_MISO: U17.5 (DIR); also elsewhere on the board
PT_DIR_SPI: U14.5 (DIR), U15.5 (DIR), U16.5 (DIR); also elsewhere on the board
PT_DIR_TX: U18.5 (DIR); also elsewhere on the board
PT_MISO: U17.3 (A); also elsewhere on the board
PT_MOSI: U15.3 (A); also elsewhere on the board
PT_RX: U19.3 (A); also elsewhere on the board
PT_SCK: U14.3 (A); also elsewhere on the board
PT_SCL_DRV: Q4.1 (G), R74.1; also elsewhere on the board
PT_SCL_IN: U20.3 (A2); also elsewhere on the board
PT_SDA_DRV: Q3.1 (G), R73.1; also elsewhere on the board
PT_SDA_IN: U20.2 (A1); also elsewhere on the board
PT_TX: U18.3 (A); also elsewhere on the board
PVCC_OFF: Q2.1 (G), R56.2; also elsewhere on the board
VBUS: C50.1, U13.6 (IN); also elsewhere on the board

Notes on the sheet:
PVCC_OFF high or FPGA unconfigured -> U13 off. J6 pin 1 = PVCC output (do not tie to a powered target supply).
SN74LVC1T45: A = FPGA (+3V3), B = J6 (PVCC), DIR high = A->B; outputs Hi-Z while PVCC is off. I2C: 2N7002 open drain + LVC2T45 input (any PVCC). JP3 = 2.2k pull-ups to PVCC.
Protocol tester: J6 = SPI / I2C / UART TTL, logic level PVCC from U13 (TLV75801P, same divider as VCCB): off, 1.8 / 2.5 / 3.3 / 4.0 / ~5 V.
